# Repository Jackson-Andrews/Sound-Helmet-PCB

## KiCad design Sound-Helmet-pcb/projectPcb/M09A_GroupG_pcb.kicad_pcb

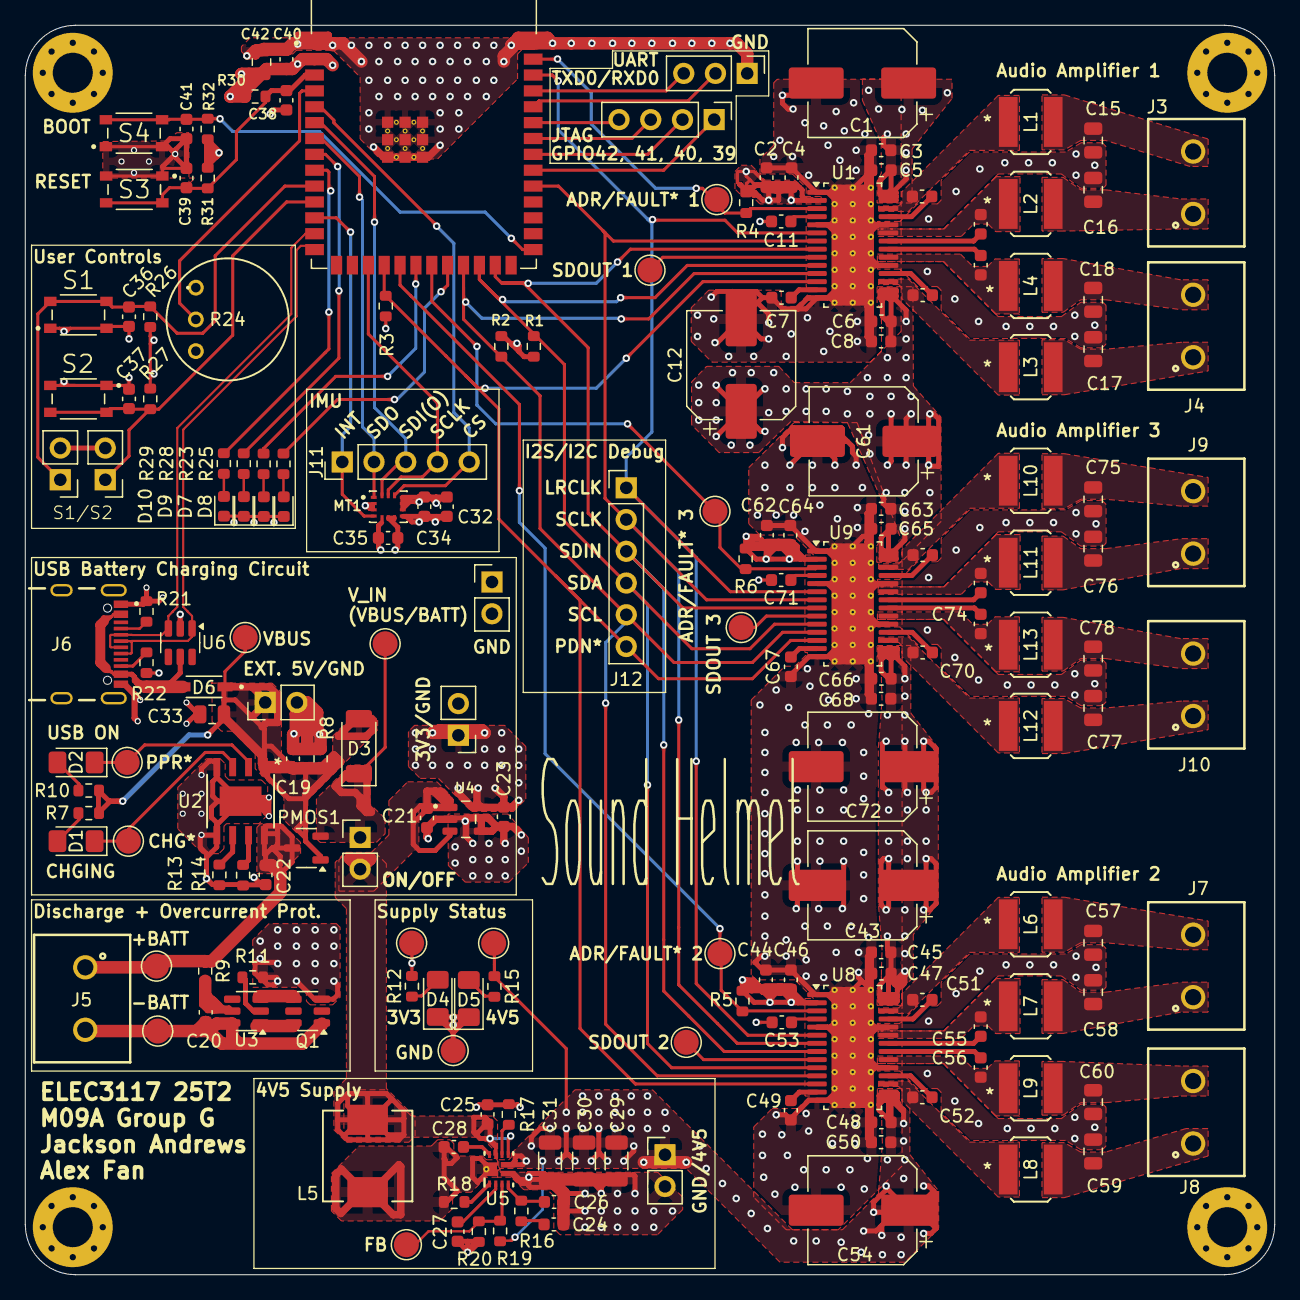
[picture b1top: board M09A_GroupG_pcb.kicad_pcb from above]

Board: 4 copper layers, 100.0 x 100.0 mm, 188 parts (0 on the bottom side), 111 nets.

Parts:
C1, C12, C43, C54, C61, C72: 390uF; CP_Elec_8x10.5
C2, C44, C62: 4.7uF; C_0603_1608Metric
C3, C8, C25, C45, C50, C63, C68: 22uF; C_0603_1608Metric
C4, C5, C6, C20, C28, C32, C36, C37, C39, C40, C41, C46, C47, C48, C64, C65, C66: 0.1uF; C_0603_1608Metric
C7, C11, C19, C21, C22, C23, C38, C49, C53, C67, C71: 1uF; C_0603_1608Metric
C9, C10, C13, C14, C51, C52, C55, C56, C69, C70, C73, C74: 0.22uF; C_0603_1608Metric
C15, C16, C17, C18, C57, C58, C59, C60, C75, C76, C77, C78: 0.68uF; C_0805_2012Metric
C24: 3.3nF; C_0603_1608Metric
C26: 12pF; C_0603_1608Metric
C27, C34: 2.2uF; C_0603_1608Metric
C29, C30, C31: 22uF; C_1206_3216Metric
C33, C42: 10uF; C_0805_2012Metric
C35: 10nF; C_0603_1608Metric
D1, D2, D4, D5: HSMG-C150; D_1206_3216Metric_Pad1.42x1.75mm_HandSolder
D3: PMEG3050EP,115; D_SOD-128
D6: 1N5819HW-7-F; SOD3715X145N
D7, D8, D9, D10: LED; LED_0603_1608Metric
H1, H2, H3, H4: MH; MountingHole_3.2mm_M3_Pad_Via
J1: UART; PinHeader_1x03_P2.54mm_Vertical
J2: JTAG debug; PinHeader_1x04_P2.54mm_Vertical
J3, J7, J9: Channel L; 691137710002
J4, J8, J10: Channel R; 691137710002
J5: BATTERY; 691137710002
J6: USB4105-GF-A; GCT_USB4105-GF-A
J11: IMU SPI; PinHeader_1x05_P2.54mm_Vertical
J12: Amplifier I2S/I2C; PinHeader_1x06_P2.54mm_Vertical
J13, J14, J17, J18, J19: PinHeader_1x02_P2.54mm_Vertical
J15: EXT. 5V; PinHeader_1x02_P2.54mm_Vertical
J16: SW ON/OFF; PinHeader_1x02_P2.54mm_Vertical
L1, L2, L3, L4, L6, L7, L8, L9, L10, L11, L12, L13: 4.7uH; IND_NRS5030T100MMGJ_TAY
L5: 1u8; IND_SRP7028A_BRN
MT1: ICM-42605; XDCR_ICM-42605
PMOS1: PMOS; SOT-23-3
Q1: FS8205; SOT-23-6
R1, R2: PU; R_0603_1608Metric
R3, R7, R8, R10, R12, R15, R26, R27, R30, R31, R32: 10k; R_0603_1608Metric
R4, R5, R6: 4.7k_15k_47k; R_0603_1608Metric
R9: 100; R_0603_1608Metric
R11: 1k; R_0603_1608Metric
R13: 200; R_0603_1608Metric
R14: 1.2k; R_0603_1608Metric
R16: 8.2k; R_0603_1608Metric
R17: 205k; R_0603_1608Metric
R18: 301k; R_0603_1608Metric
R19: 271k; R_0603_1608Metric
R20: 100k; R_0603_1608Metric
R21, R22: 5k1; R_0603_1608Metric
R23, R25, R28, R29: 330; R_0603_1608Metric
R24: VOLUME; RES3_91A_TTE_91AR10KLF
S1: CAL AUDIO DIRECTION; SW_TL3365AF180QG
S2: OTHER; SW_TL3365AF180QG
S3: RESET; SW_TL3365AF180QG
S4: BOOT; SW_TL3365AF180QG
TP1, TP10, TP11, TP13, TP19, TP20, TP21: TestPoint_Pad_D2.0mm
TP22, TP23, TP24, TP25, TP26, TP27, TP28, TP29, TP30: TestPoint; TestPoint_Pad_D2.0mm
U1, U8, U9: TAS5805MPWP; TSSOP-28-1EP_4.4x9.7mm_P0.65mm_EP3.4x9.7mm_Mask3.1x4.05mm_T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
U2: TPB4056A20-ES1R; ESOP-8_TPK
U3: DW01A; SOT-23-6
U4: TLV75733PDBVR; SOT95P280X145-5N
U5: TPS61089RNRR; UltraLibrarian_TPS61089RNRR_RNR0011A
U6: SRV05-4; SOT-23-6
U7: ESP32-S3-WROOM-1-N8R8; XCVR_ESP32S3WROOM1N8R8

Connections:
+3V3: C2.1, C4.1, C23.1, C32.1, C34.1, C35.1, C40.1, C42.1, C44.1, C46.1, C62.1, C64.1, J17.1, MT1.5 (VDDIO), MT1.8 (VDD), R1.1, R2.1, R3.1, R4.1, R5.1, R6.1, R12.1, R24.3, R26.1, R27.1, R30.1, R31.1, R32.1, TP28.1, U1.2 (DVDD), U4.5 (OUT), U7.2 (3V3), U8.2 (DVDD), U9.2 (DVDD)
+BATT: C22.1, J5.1, PMOS1.3 (D), R9.1, TP24.1, U2.8 (BAT)
-BATT: C20.2, J5.2, Q1.1, TP25.1, U3.6 (GND)
/Audio Amplifier 1/ADR/FAULT\: R4.2, TP13.1, U1.3 (ADR/~FAULT), U7.39 (IO1)
/Audio Amplifier 1/LRCLK: J12.1, U1.6 (LRCLK), U7.38 (IO2), U8.6 (LRCLK), U9.6 (LRCLK)
/Audio Amplifier 1/PDN\: J12.6, R3.2, U1.12 (~PDN), U7.18 (IO10), U8.12 (~PDN), U9.12 (~PDN)
/Audio Amplifier 1/PVDD_4V5: C1.1, C3.1, C5.1, C6.1, C8.1, C12.1, C29.1, C30.1, C31.1, C43.1, C45.1, C47.1, C48.1, C50.1, C54.1, C61.1, C63.1, C65.1, C66.1, C68.1, C72.1, J18.1, R15.1, R19.1, TP29.1, U1.15 (PVDD), U1.16 (PVDD), U1.27 (PVDD), U1.28 (PVDD), U5.6 (VOUT), U8.15 (PVDD), U8.16 (PVDD), U8.27 (PVDD), U8.28 (PVDD), U9.15 (PVDD), U9.16 (PVDD), U9.27 (PVDD), U9.28 (PVDD)
/Audio Amplifier 1/SCL: J12.5, R2.2, U1.11 (SCL), U7.23 (IO21), U8.11 (SCL), U9.11 (SCL)
/Audio Amplifier 1/SCLK: J12.2, U1.7 (SCLK), U7.31 (IO38), U8.7 (SCLK), U9.7 (SCLK)
/Audio Amplifier 1/SDA: J12.4, R1.2, U1.10 (SDA), U7.24 (IO47), U8.10 (SDA), U9.10 (SDA)
/Audio Amplifier 1/SDIN: J12.3, U1.8 (SDIN), U7.25 (IO48), U8.8 (SDIN), U9.8 (SDIN)
/Audio Amplifier 1/SDOUT: TP19.1, U1.9 (SDOUT)
/Audio Amplifier 2/ADR/FAULT\: R5.2, TP11.1, U7.19 (IO11), U8.3 (ADR/~FAULT)
/Audio Amplifier 2/SDOUT: TP20.1, U8.9 (SDOUT)
/Audio Amplifier 3/ADR/FAULT\: R6.2, TP10.1, U7.21 (IO13), U9.3 (ADR/~FAULT)
/Audio Amplifier 3/SDOUT: TP21.1, U9.9 (SDOUT)
/Main Compute Module/CHIP_PU: C38.1, C39.1, R30.2, R31.2, S3.3, S3.4, U7.3 (EN)
/Main Compute Module/D+: J6.A6 (DP1), J6.B6 (DP2), U6.1 (IO1), U7.14 (IO20)
/Main Compute Module/D-: J6.A7 (DN1), J6.B7 (DN2), U6.3 (IO2), U7.13 (IO19)
/Main Compute Module/GPIO0: C41.1, R32.2, S4.3, S4.4, U7.27 (IO0)
/Main Compute Module/GPIO4: R24.2, U7.4 (IO4)
/Main Compute Module/GPIO5: J11.5, MT1.12 (AP_CS), U7.5 (IO5)
/Main Compute Module/GPIO6: J11.3, MT1.14 (AP_SDA/AP_SDIO/AP_SDI), U7.6 (IO6)
/Main Compute Module/GPIO7: J11.2, MT1.1 (AP_SDO/AP_AD0), U7.7 (IO7)
/Main Compute Module/GPIO9: J11.4, MT1.13 (AP_SCL/AP_SCLK), U7.17 (IO9)
/Main Compute Module/GPIO12: R23.1, U7.20 (IO12)
/Main Compute Module/GPIO14: R25.1, U7.22 (IO14)
/Main Compute Module/GPIO15: R28.1, U7.8 (IO15)
/Main Compute Module/GPIO16: R29.1, U7.9 (IO16)
/Main Compute Module/GPIO17: C36.1, J13.1, R26.2, S1.3, S1.4, U7.10 (IO17)
/Main Compute Module/GPIO18: C37.1, J14.1, R27.2, S2.3, S2.4, U7.11 (IO18)
/Main Compute Module/GPIO39: J2.1, U7.32 (IO39)
/Main Compute Module/GPIO40: J2.2, U7.33 (IO40)
/Main Compute Module/GPIO41: J2.3, U7.34 (IO41)
/Main Compute Module/GPIO42: J2.4, U7.35 (IO42)
/Main Compute Module/INT: J11.1, MT1.4 (INT1/INT), U7.12 (IO8)
/Main Compute Module/RXD0: J1.2, U7.36 (RXD0)
/Main Compute Module/TXD0: J1.3, U7.37 (TXD0)
GND: C1.2, C2.2, C3.2, C4.2, C5.2, C6.2, C7.2, C8.2, C11.2, C12.2, C15.2, C16.2, C17.2, C18.2, C19.2, C21.2, C22.2, C23.2, C24.2, C25.2, C26.2, C27.2, C29.2, C30.2, C31.2, C32.2, C33.2, C34.2, C35.2, C36.2, C37.2, C38.2, C39.2, C40.2, C41.2, C42.2, C43.2, C44.2, C45.2, C46.2, C47.2, C48.2, C49.2, C50.2, C53.2, C54.2, C57.2, C58.2, C59.2, C60.2, C61.2, C62.2, C63.2, C64.2, C65.2, C66.2, C67.2, C68.2, C71.2, C72.2, C75.2, C76.2, C77.2, C78.2, D4.1 (K), D5.1 (K), D7.1 (K), D8.1 (K), D9.1 (K), D10.1 (K), H1.1, H2.1, H3.1, H4.1, J1.1, J6.A1_B12 (GND), J6.B1_A12 (GND__1), J6.SH1 (SHELL_GND), J6.SH2 (SHELL_GND__1), J6.SH3 (SHELL_GND__2), J6.SH4 (SHELL_GND__3), J13.2, J14.2, J15.2, J17.2, J18.2, J19.1, J19.2, MT1.2 (RESV), MT1.3 (RESV__1), MT1.6 (GND), MT1.7 (RESV__2), MT1.9 (INT2/FSYNC), MT1.10 (RESV__3), MT1.11 (RESV__4), Q1.3, R8.2, R11.1, R13.2, R14.2, R17.2, R20.2, R21.2, R22.2, R24.1, S1.1, S1.2, S2.1, S2.2, S3.1, S3.2, S4.1, S4.2, TP1.1, U1.1 (DGND), U1.5 (DGND), U1.14 (AGND), U1.19 (PGND), U1.24 (PGND), U1.29 (EP), U2.4 (*EN), U2.5 (GND), U2.9 (GND), U4.2 (GND), U4.4 (NC), U5.5 (GND), U6.2 (VN), U7.1 (GND), U7.40 (GND__1), U7.41_1 (GND__2), U7.41_2 (GND__3), U7.41_3 (GND__4), U7.41_4 (GND__5), U7.41_5 (GND__6), U7.41_6 (GND__7), U7.41_7 (GND__8), U7.41_8 (GND__9), U7.41_9 (GND__10), U7.41_10 (GND_VIA), U7.41_11 (GND_VIA), U7.41_12 (GND_VIA), U7.41_13 (GND_VIA), U7.41_14 (GND_VIA), U7.41_15 (GND_VIA), U7.41_16 (GND_VIA), U7.41_17 (GND_VIA), U7.41_18 (GND_VIA), U7.41_19 (GND_VIA), U7.41_20 (GND_VIA), U7.41_21 (GND_VIA), U8.1 (DGND), U8.5 (DGND), U8.14 (AGND), U8.19 (PGND), U8.24 (PGND), U8.29 (EP), U9.1 (DGND), U9.5 (DGND), U9.14 (AGND), U9.19 (PGND), U9.24 (PGND), U9.29 (EP)
unnamed: C15.1, J3.2, L1.2
unnamed: C16.1, J3.1, L2.2
unnamed: C17.1, J4.1, L3.2
unnamed: C18.1, J4.2, L4.2
unnamed: C24.1, R16.2
unnamed: C57.1, J7.2, L6.2
unnamed: C58.1, J7.1, L7.2
unnamed: C59.1, J8.1, L8.2
unnamed: C60.1, J8.2, L9.2
unnamed: C75.1, J9.2, L10.2
unnamed: C76.1, J9.1, L11.2
unnamed: C77.1, J10.1, L12.2
unnamed: C78.1, J10.2, L13.2
unnamed: D1.2 (A), R7.2
unnamed: D1.1 (K), TP23.1, U2.3 (*CHG)
unnamed: D2.2 (A), R10.2
unnamed: D2.1 (K), TP27.1, U2.2 (*PPR)
unnamed: D3.1 (K), J16.1, PMOS1.2 (S), TP26.1
unnamed: D4.2 (A), R12.2
unnamed: D5.2 (A), R15.2
unnamed: D7.2 (A), R23.2
unnamed: D8.2 (A), R25.2
unnamed: D9.2 (A), R28.2
unnamed: D10.2 (A), R29.2
unnamed: J6.A5 (CC1), R21.1
unnamed: J6.B5 (CC2), R22.1
unnamed: D6.A, J6.A4_B9 (VBUS), J6.B4_A9 (VBUS__1), U6.5 (VP)
unnamed: C7.1, U1.13 (AVDD)
unnamed: C9.1, U1.25 (BST_A+)
unnamed: C13.1, U1.22 (BST_A-)
unnamed: C10.1, U1.18 (BST_B+)
unnamed: C14.1, U1.21 (BST_B-)
unnamed: C9.2, L1.1, U1.26 (OUT_A+)
unnamed: C13.2, L2.1, U1.23 (OUT_A-)
unnamed: C10.2, L3.1, U1.17 (OUT_B+)
unnamed: C14.2, L4.1, U1.20 (OUT_B-)
unnamed: C11.1, U1.4 (VR_DIG)
unnamed: R13.1, U2.6 (IMIN)
unnamed: R14.1, U2.7 (IREF)
unnamed: R11.2, U3.2 (CS)
unnamed: Q1.4, U3.3 (OC)
unnamed: Q1.6, U3.1 (OD)
unnamed: C20.1, R9.2, U3.5 (VCC)
unnamed: C28.1, U5.10 (BOOT)
unnamed: C26.1, R16.1, U5.4 (COMP)
unnamed: R19.2, R20.1, TP30.1, U5.3 (FB)
unnamed: R18.2, U5.1 (FSW)
unnamed: R17.1, U5.8 (ILIM)
unnamed: C28.2, L5.2, R18.1, U5.11 (SW), U5.V (SW_VIA)
unnamed: C27.1, U5.2 (VCC)
unnamed: C49.1, U8.13 (AVDD)
unnamed: C51.1, U8.25 (BST_A+)
unnamed: C55.1, U8.22 (BST_A-)
unnamed: C52.1, U8.18 (BST_B+)
unnamed: C56.1, U8.21 (BST_B-)
unnamed: C51.2, L6.1, U8.26 (OUT_A+)
unnamed: C55.2, L7.1, U8.23 (OUT_A-)
unnamed: C52.2, L8.1, U8.17 (OUT_B+)
unnamed: C56.2, L9.1, U8.20 (OUT_B-)
unnamed: C53.1, U8.4 (VR_DIG)
unnamed: C67.1, U9.13 (AVDD)
unnamed: C69.1, U9.25 (BST_A+)
unnamed: C73.1, U9.22 (BST_A-)
unnamed: C70.1, U9.18 (BST_B+)
unnamed: C74.1, U9.21 (BST_B-)
unnamed: C69.2, L10.1, U9.26 (OUT_A+)
unnamed: C73.2, L11.1, U9.23 (OUT_A-)
unnamed: C70.2, L12.1, U9.17 (OUT_B+)
unnamed: C74.2, L13.1, U9.20 (OUT_B-)
unnamed: C71.1, U9.4 (VR_DIG)
VBUS: C19.1, C33.1, D3.2 (A), D6.C, J15.1, PMOS1.1 (G), R7.1, R8.1, R10.1, TP22.1, U2.1 (VIN)
V_IN: C21.1, C25.1, J16.2, L5.1, U4.1 (IN), U4.3 (EN), U5.7 (EN), U5.9 (VIN)

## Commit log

2026-05-31 All files added
2026-05-31 Readded all files
